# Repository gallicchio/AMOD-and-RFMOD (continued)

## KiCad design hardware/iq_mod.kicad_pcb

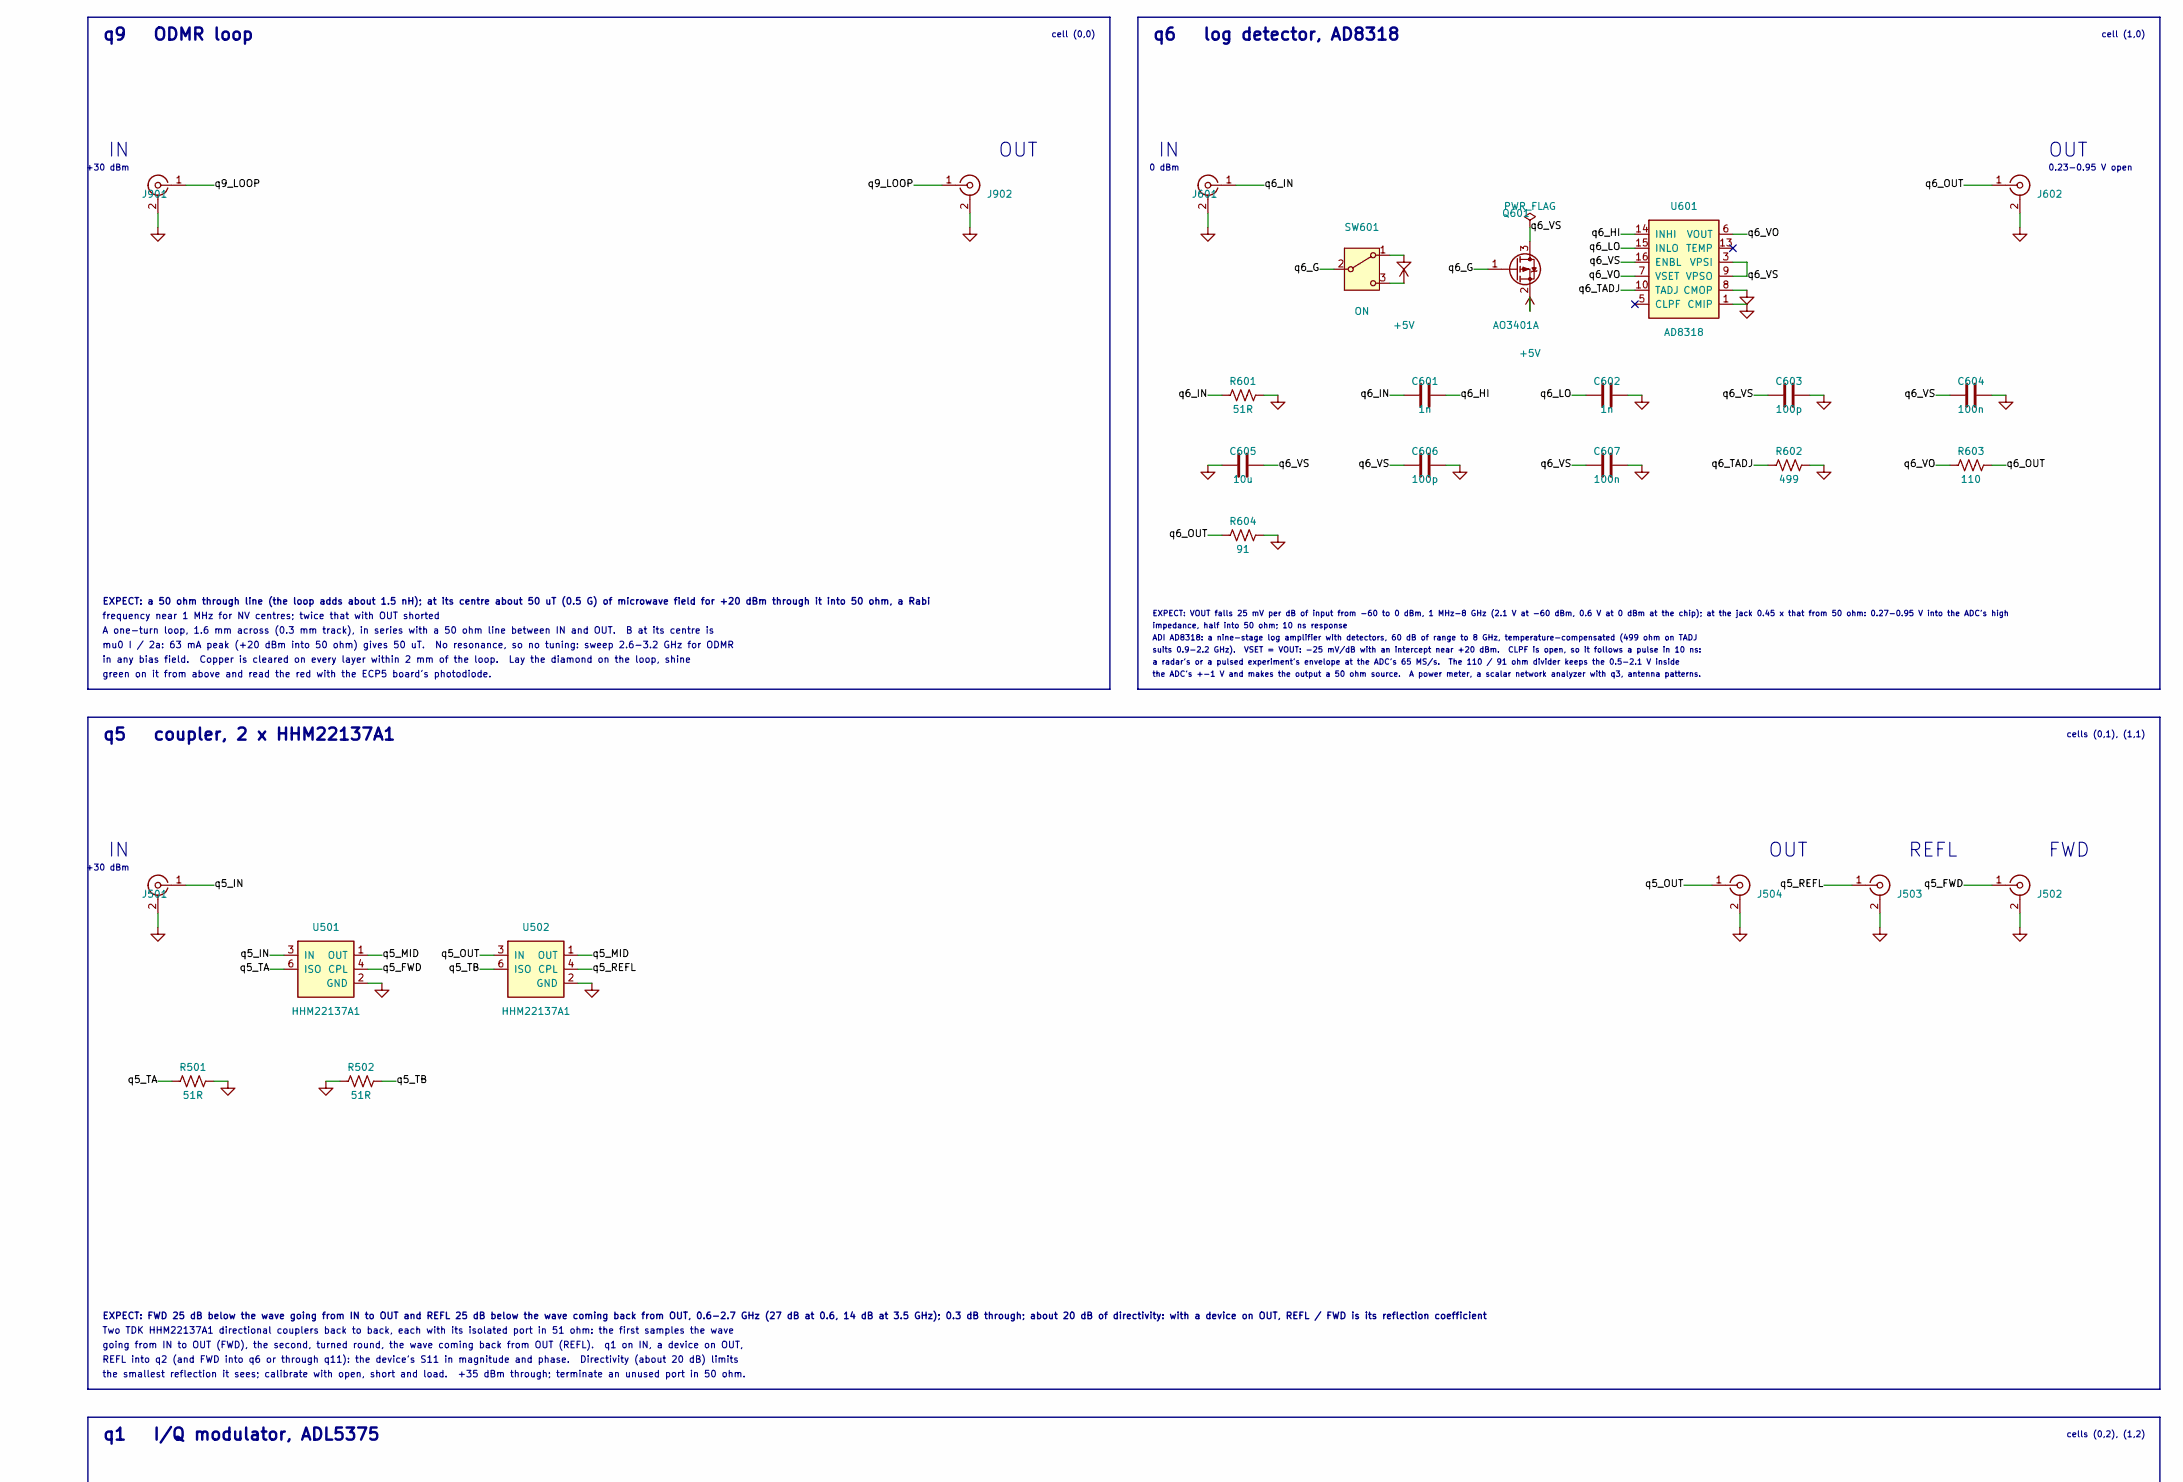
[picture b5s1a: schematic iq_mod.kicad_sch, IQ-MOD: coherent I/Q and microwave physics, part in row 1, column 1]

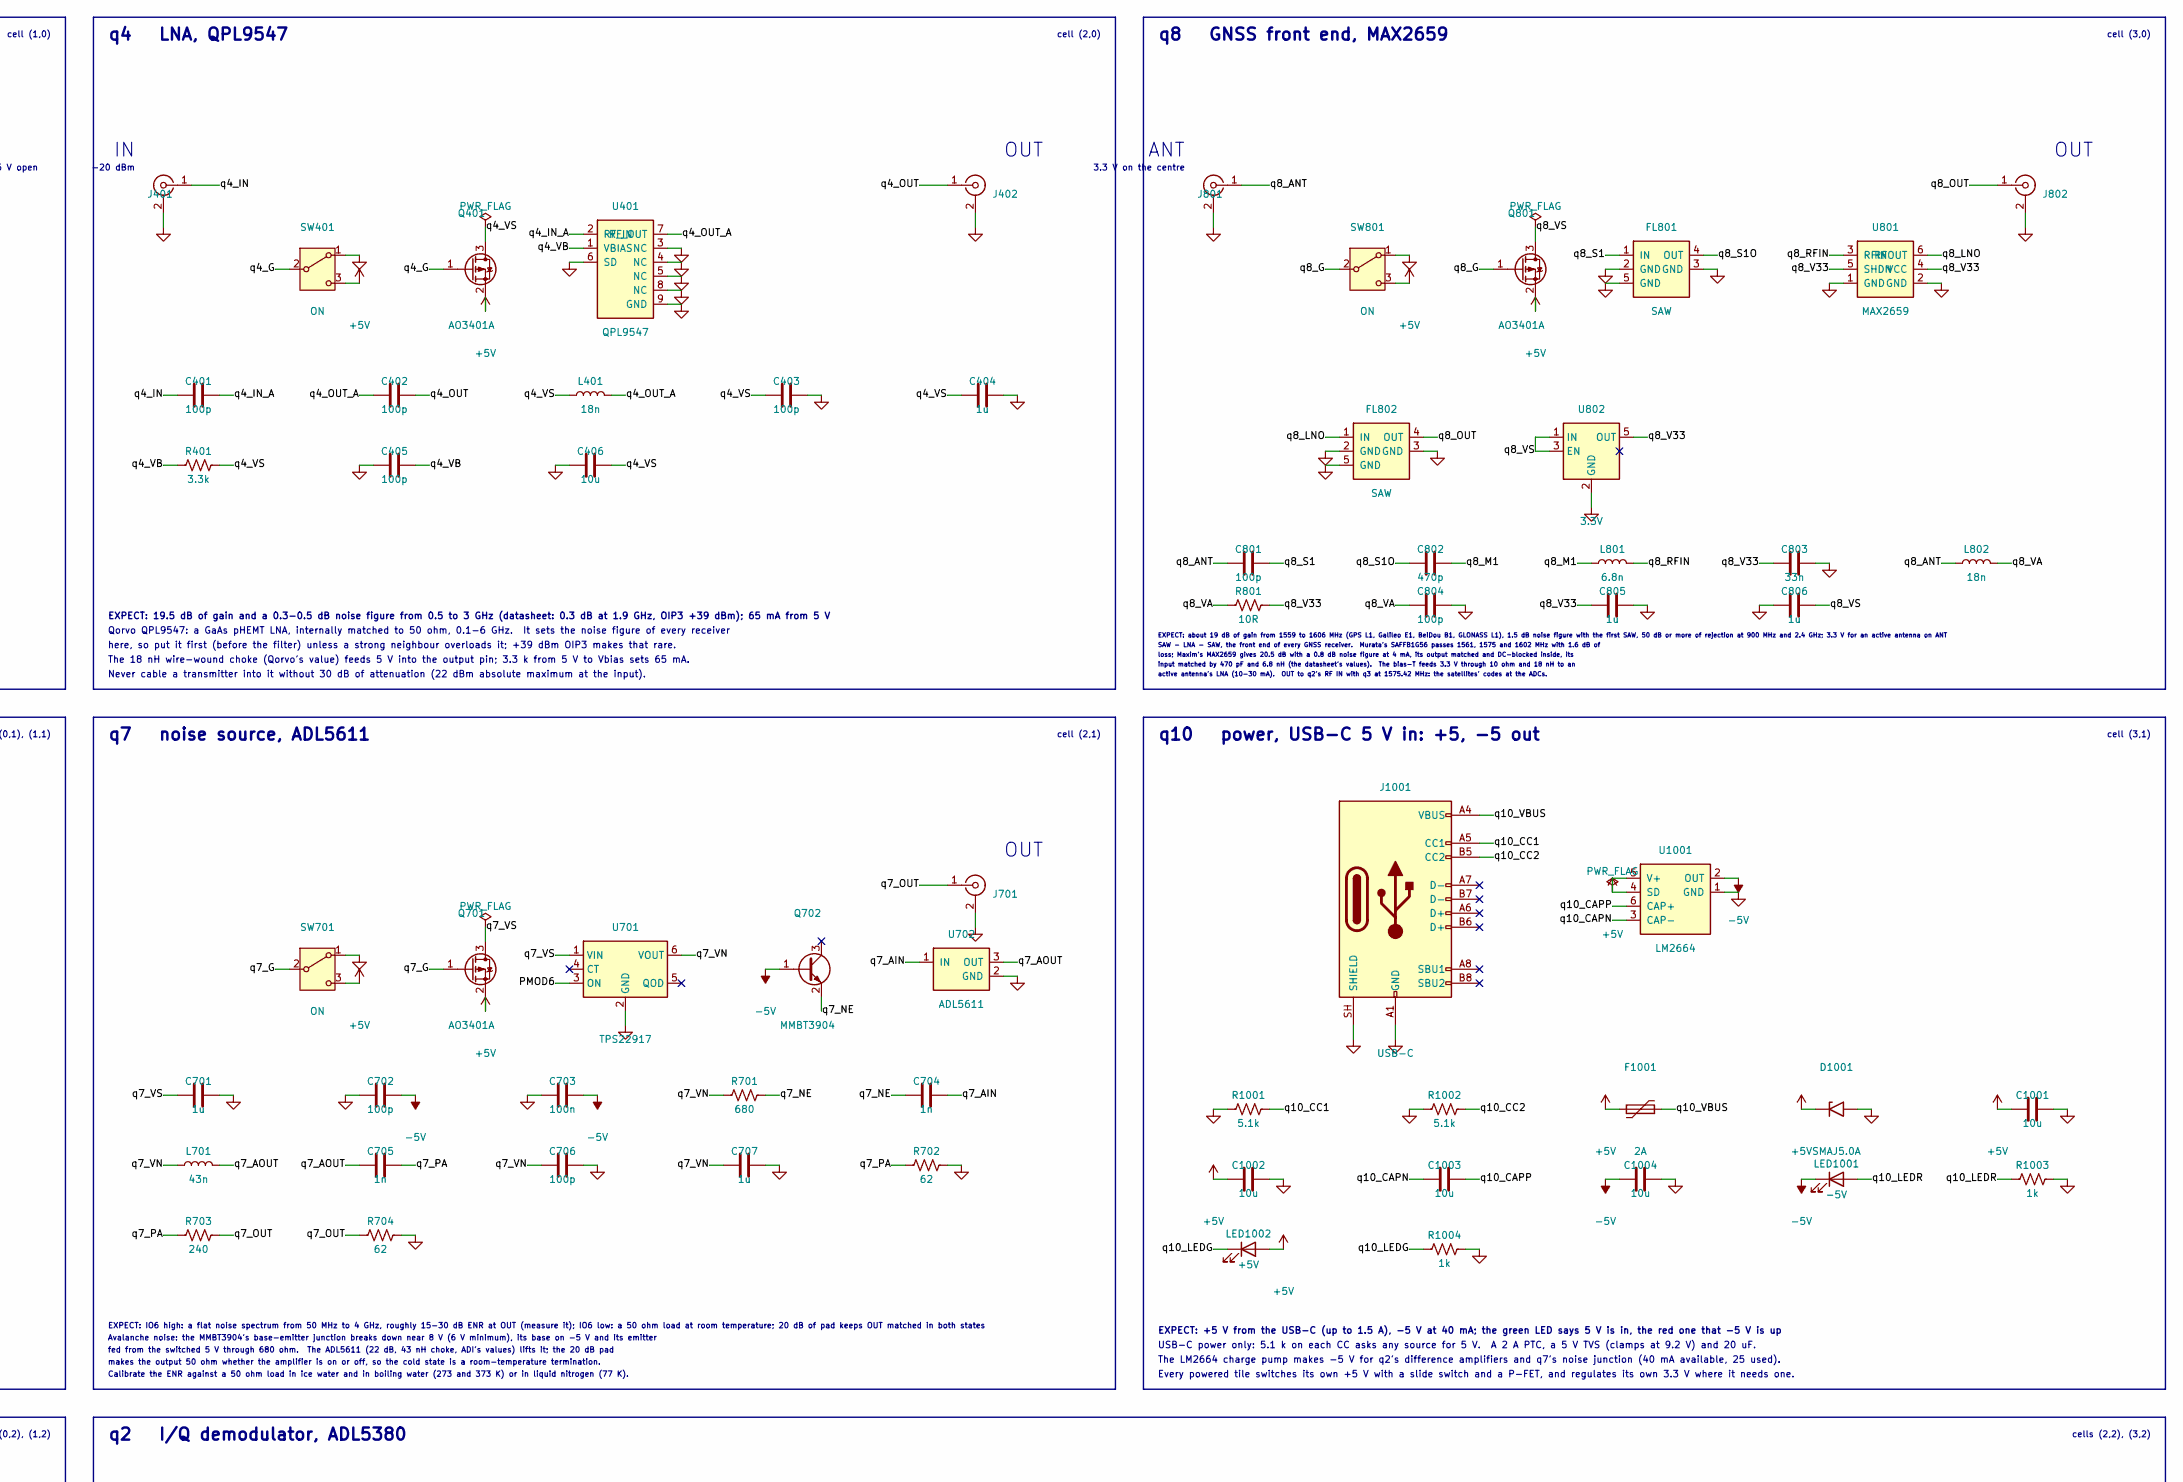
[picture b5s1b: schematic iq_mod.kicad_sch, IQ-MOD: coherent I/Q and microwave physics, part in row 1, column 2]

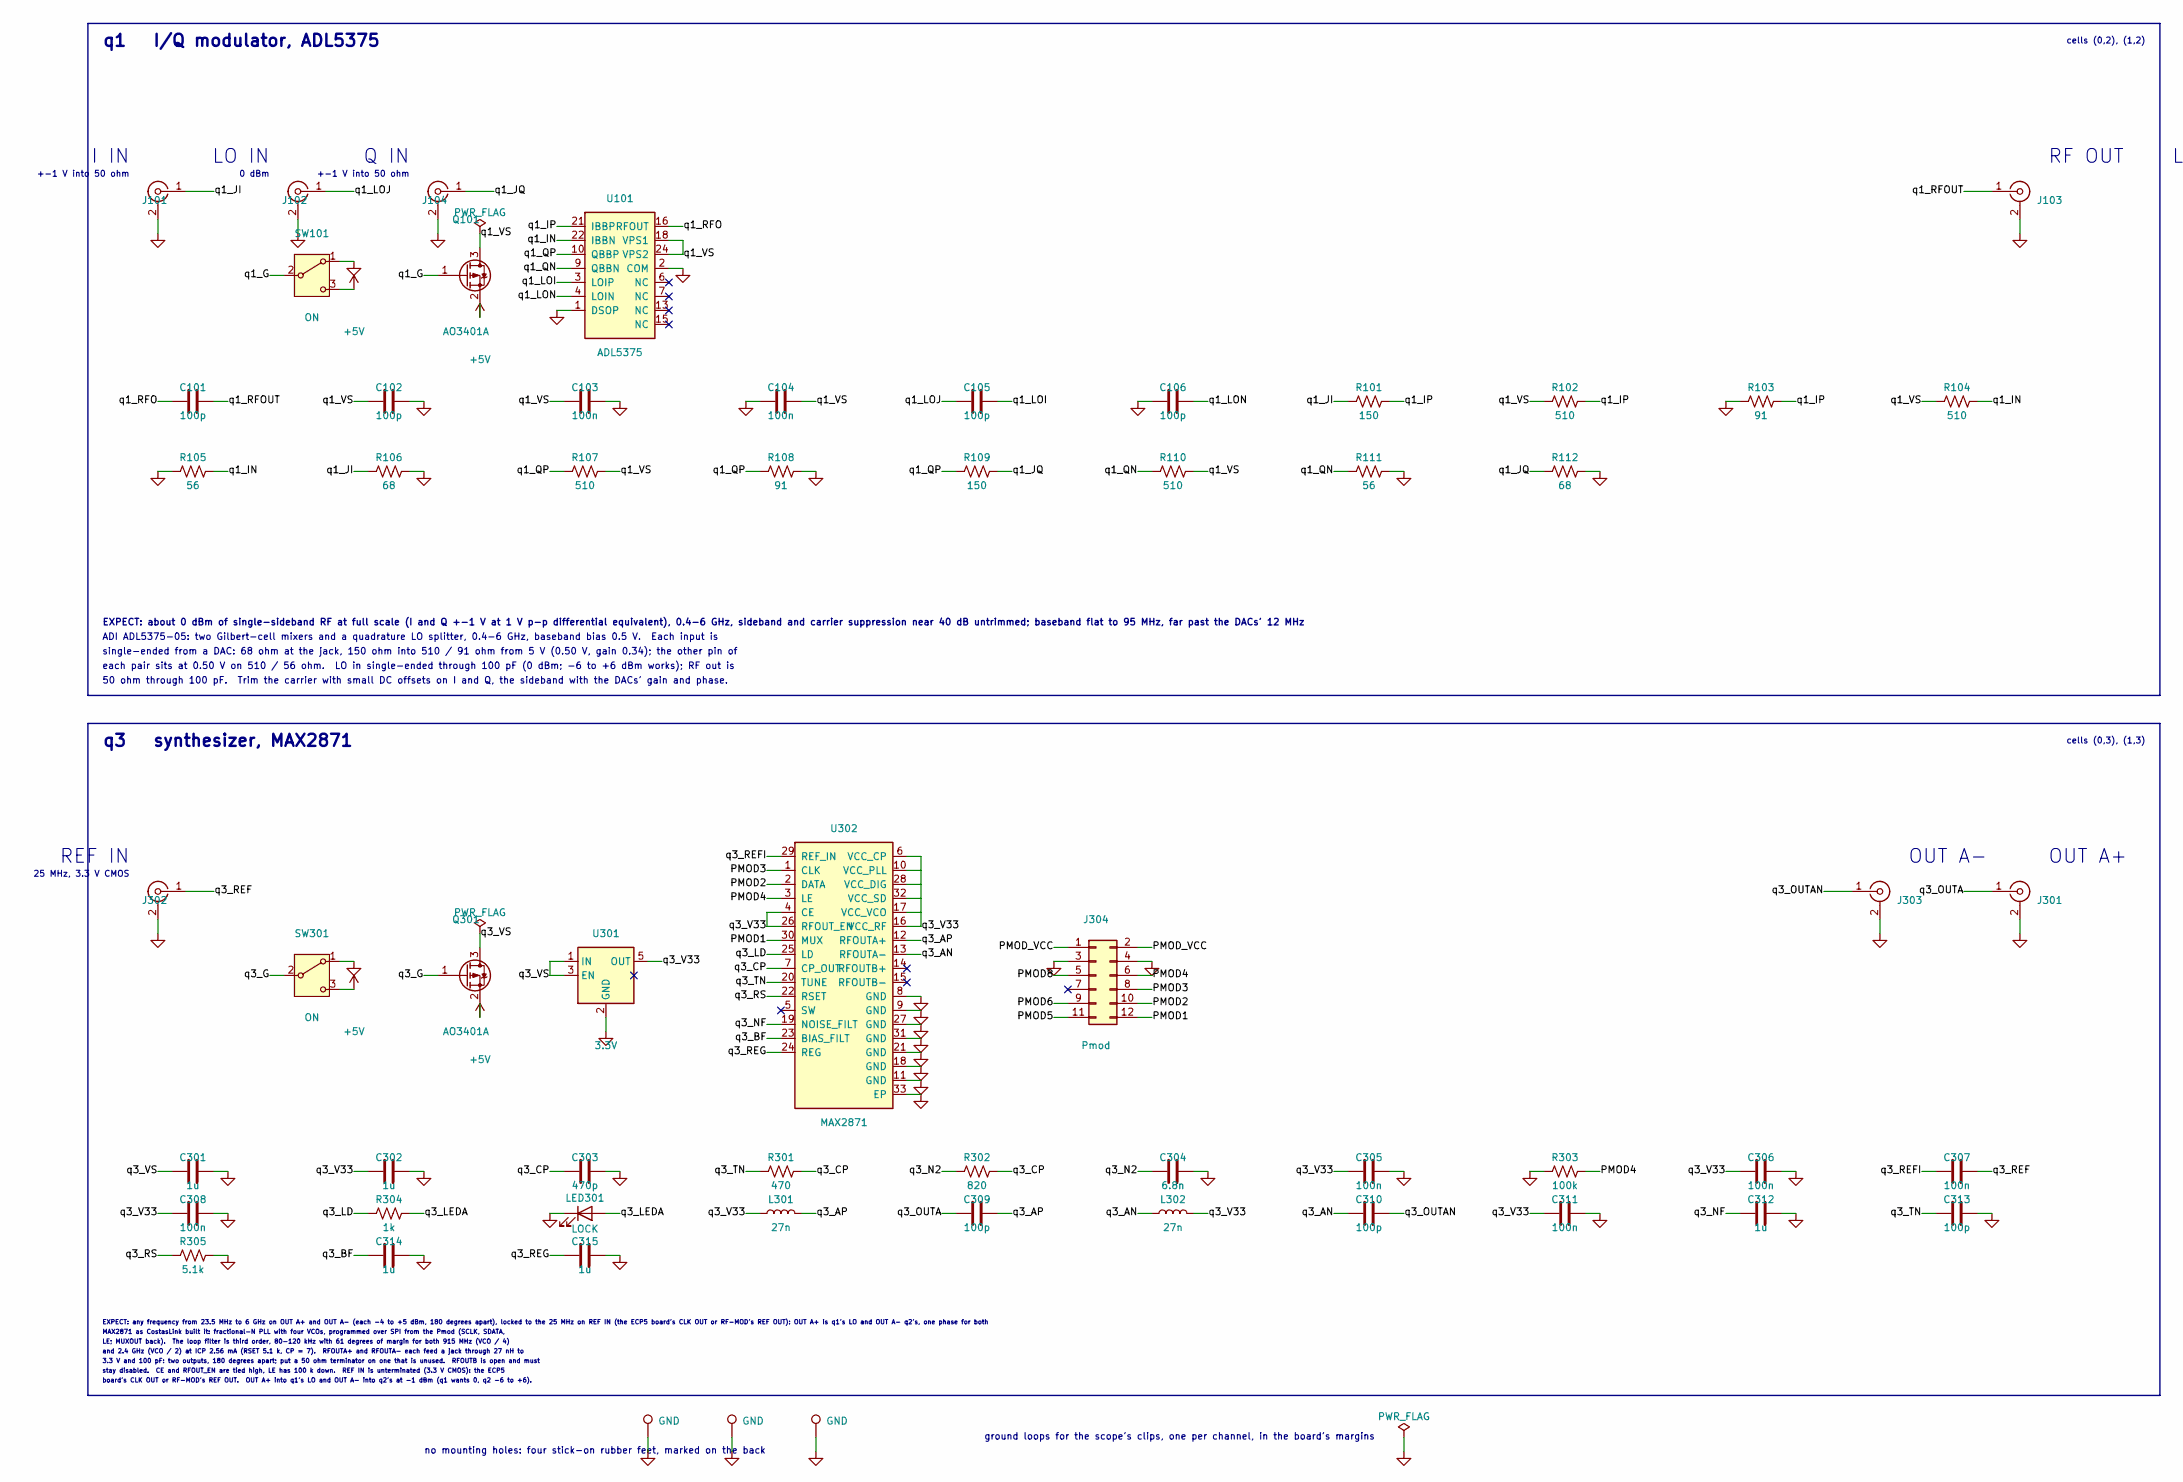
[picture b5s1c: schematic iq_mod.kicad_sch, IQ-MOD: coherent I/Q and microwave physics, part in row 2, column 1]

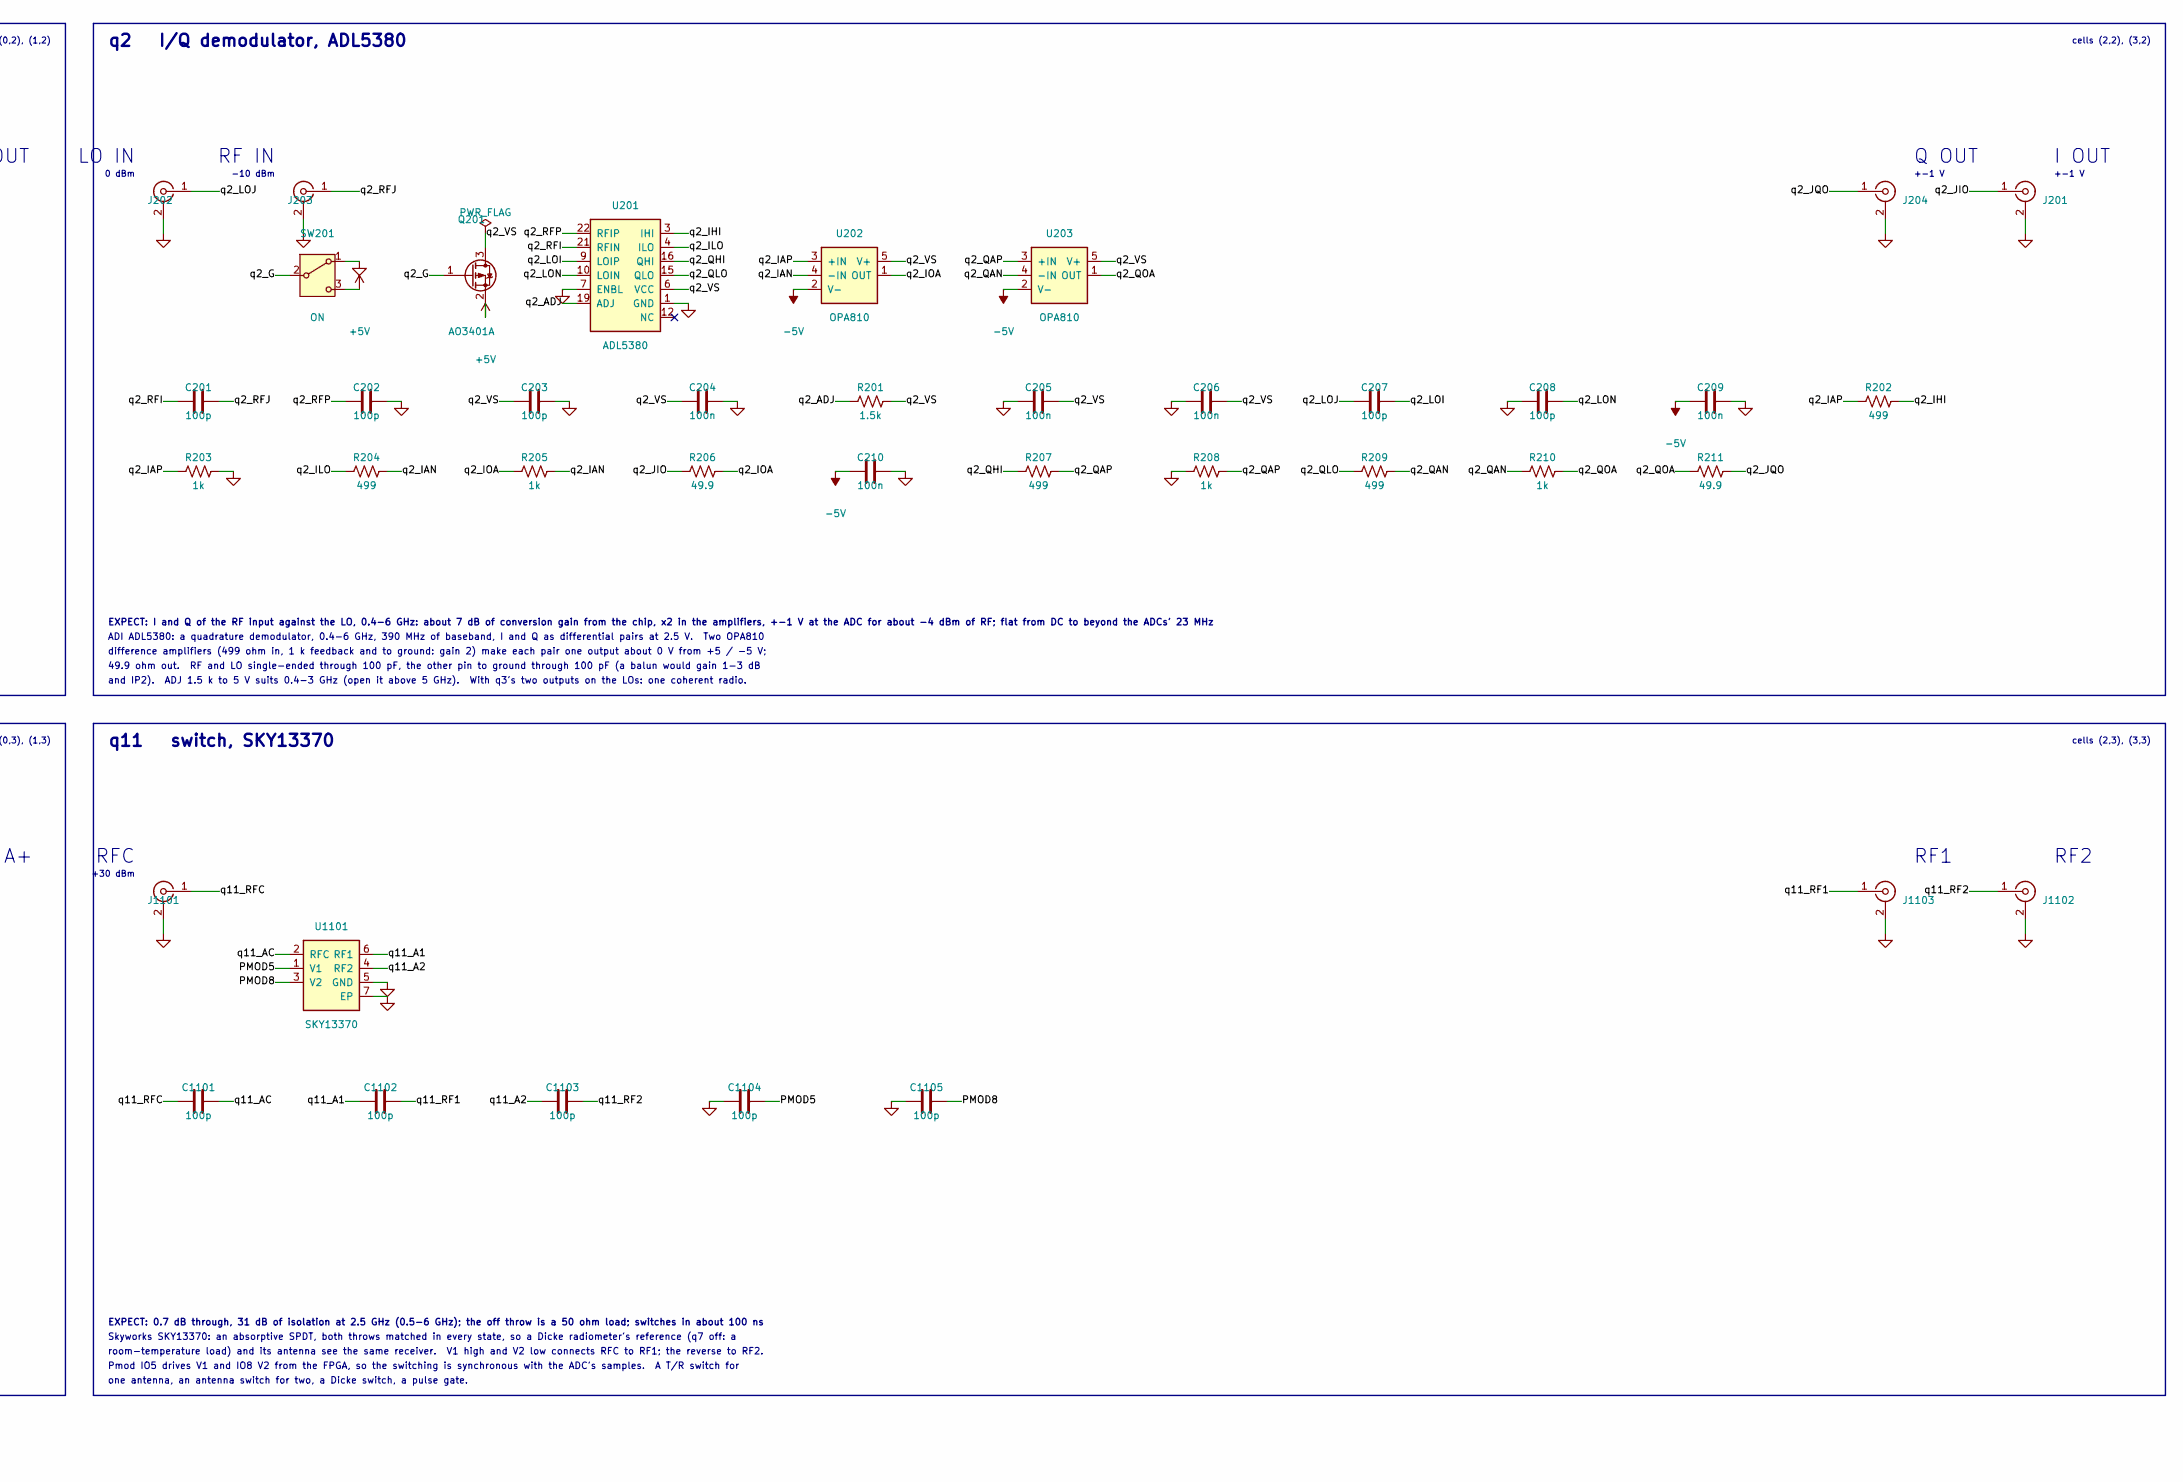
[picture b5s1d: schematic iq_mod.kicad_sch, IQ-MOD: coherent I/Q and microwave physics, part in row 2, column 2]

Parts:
C101, C102, C105, C106, C201, C202, C203, C207, C208, C309, C310, C401, C402, C403, C405, C603, C606, C702, C706, C801, C804, C1101, C1102, C1103, C1104, C1105: 100p; C_0402_1005Metric; MPN 0402CG101J500NT; LCSC C1546
C103, C104, C204, C205, C206, C209, C210, C305, C306, C307, C308, C311, C604, C607, C703: 100n; C_0402_1005Metric; MPN CL05B104KO5NNNC; LCSC C1525
C301, C302: 1u; C_0805_2012Metric; MPN CL21B105KBFNNNE; LCSC C28323
C303: 470p; C_0603_1608Metric; MPN 0603CG471J500NT; LCSC C36252
C304: 6.8n; C_0603_1608Metric; MPN GRM1885C1H682JA01D; LCSC C162241
C312, C314, C315, C404, C701, C707, C805, C806: 1u; C_0402_1005Metric; MPN CL05A105KP5NNNC; LCSC C14445
C313: 100p; C_0603_1608Metric; MPN CL10C101JB8NNNC; LCSC C14858
C406, C605, C1001, C1002, C1003, C1004: 10u; C_0805_2012Metric; MPN CL21A106KAYNNNE; LCSC C15850
C601, C602, C704, C705: 1n; C_0402_1005Metric; MPN 0402B102K500NT; LCSC C1523
C802: 470p; C_0402_1005Metric; MPN 0402CG471J500NT; LCSC C75274
C803: 33n; C_0402_1005Metric; MPN FCC0402B333K500AT; LCSC C7419416
D1001: SMAJ5.0A; D_SMA; MPN SMAJ5.0A; LCSC C78401
F1001: 2A; Fuse_1812_4532Metric; MPN MF-MSMF200-2; LCSC C210837
FL801, FL802: SAW; Filter_SAW_1109-5P_SAFFB1G56; MPN SAFFB1G56KB0F0AR1X; LCSC C91647
J101, J102, J103, J104, J201, J202, J203, J204, J301, J302, J303, J401, J402, J501, J502, J503, J504, J601, J602, J701, J801, J802, J901, J902, J1101, J1102, J1103: SMA; SMA_BWSMA-KE-Z001_Vertical; MPN BWSMA-KE-Z001; LCSC C496549
J304: Pmod; PinHeader_2x06_P2.54mm_Horizontal_PZ254R-12-12P; MPN PZ254R-12-12P; LCSC C492434
J1001: USB-C; USB_C_Receptacle_HRO_TYPE-C-31-M-12; MPN TYPE-C-31-M-12; LCSC C165948
L301, L302: 27n; L_0402_1005Metric; MPN LQW15AN27NG80D; LCSC C882469
L401, L802: 18n; L_0402_1005Metric; MPN LQW15AN18NG00D; LCSC C91622
L701: 43n; L_0603_1608Metric; MPN LQW18AN43NG00D; LCSC C113126
L801: 6.8n; L_0402_1005Metric; MPN LQW15AN6N8G00D; LCSC C82919
LED301: LOCK; LED_0805_2012Metric_Kbar; MPN NCD0805R1; LCSC C84256
LED1001: -5V; LED_0805_2012Metric_Kbar; MPN NCD0805R1; LCSC C84256
LED1002: +5V; LED_0805_2012Metric_Kbar; MPN KT-0805G; LCSC C2297
Q101, Q201, Q301, Q401, Q601, Q701, Q801: AO3401A; SOT-23; MPN AO3401A; LCSC C15127
Q702: MMBT3904; SOT-23; MPN MMBT3904(RANGE:100-300); LCSC C20526
R101, R109: 150; R_0402_1005Metric; MPN 0402WGF1500TCE; LCSC C25082
R102, R104, R107, R110: 510; R_0402_1005Metric; MPN 0402WGF5100TCE; LCSC C25123
R103, R108, R604: 91; R_0402_1005Metric; MPN 0402WGF910JTCE; LCSC C270574
R105, R111: 56; R_0402_1005Metric; MPN 0402WGF560JTCE; LCSC C25127
R106, R112: 68; R_0402_1005Metric; MPN 0402WGF680JTCE; LCSC C25131
R201: 1.5k; R_0402_1005Metric; MPN 0402WGF1501TCE; LCSC C25867
R202, R204, R207, R209, R602: 499; R_0402_1005Metric; MPN 0402WGF4990TCE; LCSC C4125
R203, R205, R208, R210, R304: 1k; R_0402_1005Metric; MPN 0402WGF1001TCE; LCSC C11702
R206, R211: 49.9; R_0402_1005Metric; MPN CRCW040249R9FKEDHP; LCSC C844112
R301: 470; R_0402_1005Metric; MPN 0402WGF4700TCE; LCSC C25117
R302: 820; R_0402_1005Metric; MPN 0402WGF8200TCE; LCSC C25135
R303: 100k; R_0402_1005Metric; MPN 0402WGF1003TCE; LCSC C25741
R305: 5.1k; R_0402_1005Metric; MPN 0402WGF5101TCE; LCSC C25905
R401: 3.3k; R_0402_1005Metric; MPN 0402WGF3301TCE; LCSC C25890
R501, R502, R601: 51R; R_0402_1005Metric; MPN 0402WGF510JTCE; LCSC C25125
R603: 110; R_0402_1005Metric; MPN 0402WGF1100TCE; LCSC C25078
R701: 680; R_0402_1005Metric; MPN 0402WGF6800TCE; LCSC C25130
R702, R704: 62; R_0402_1005Metric; MPN 0402WGF620JTCE; LCSC C4962
R703: 240; R_0402_1005Metric; MPN 0402WGF2400TCE; LCSC C25094
R801: 10R; R_0402_1005Metric; MPN 0402WGF100JTCE; LCSC C25077
R1001, R1002: 5.1k; R_0805_2012Metric; MPN 0805W8F5101T5E; LCSC C27834
R1003, R1004: 1k; R_0805_2012Metric; MPN 0805W8F1001T5E; LCSC C17513
SW101, SW201, SW301, SW401, SW601, SW701, SW801: ON; SW_SPDT_Shouhan_MSK12C02; MPN MSK12C02; LCSC C431540
TP9901, TP9902, TP9903: GND; TestPoint_Loop_RH-5019; MPN RH-5019; LCSC C5199800
U101: ADL5375; QFN-24-1EP_4x4mm_P0.5mm_EP2.5x2.5mm; MPN ADL5375-05ACPZ-R7; LCSC C579150
U201: ADL5380; QFN-24-1EP_4x4mm_P0.5mm_EP2.5x2.5mm; MPN ADL5380ACPZ-R7; LCSC C579152
U202, U203: OPA810; SOT-23-5; MPN OPA810IDBVR; LCSC C2833513
U301, U802: 3.3V; SOT-23-5; MPN TPS7A2033PDBVR; LCSC C2862740
U302: MAX2871; QFN-32-1EP_5x5mm_P0.5mm_EP3.1x3.1mm; MPN MAX2871ETJ+T; LCSC C7458627
U401: QPL9547; DFN-8-1EP_2x2mm_P0.5mm_EP0.9x1.6mm; MPN QPL9547TR7; LCSC C5367093
U501, U502: HHM22137A1; Coupler_1608-6P_HHM22137A1; MPN HHM22137A1; LCSC C415328
U601: AD8318; QFN-16-1EP_4x4mm_P0.65mm_EP2.1x2.1mm; MPN AD8318ACPZ-REEL7; LCSC C578694
U701: TPS22917; SOT-23-6; MPN TPS22917DBVR; LCSC C2681320
U702: ADL5611; SOT-89-3; MPN ADL5611ARKZ-R7; LCSC C208262
U801: MAX2659; UDFN-6_1.5x1.0mm_P0.5mm_MAX2659; MPN MAX2659ELT+T; LCSC C28043
U1001: LM2664; SOT-23-6; MPN LM2664M6X/NOPB; LCSC C108573
U1101: SKY13370; DFN-6-1EP_1.5x1.5mm_P0.5mm_SKY13370; MPN SKY13370-374LF; LCSC C105628

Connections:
+5V: C1001.1, C1002.1, D1001.1 (A1), F1001.1, LED1002.2 (A), Q101.2 (S), Q201.2 (S), Q301.2 (S), Q401.2 (S), Q601.2 (S), Q701.2 (S), Q801.2 (S), SW101.3 (C), SW201.3 (C), SW301.3 (C), SW401.3 (C), SW601.3 (C), SW701.3 (C), SW801.3 (C), U1001.4 (SD), U1001.5 (V+)
-5V: C209.1, C210.1, C702.2, C703.2, C1004.1, LED1001.1 (K), Q702.1 (B), U202.2 (V-), U203.2 (V-), U1001.2 (OUT)
/PMOD1: J304.12, U302.30 (MUX)
/PMOD2: J304.10, U302.2 (DATA)
/PMOD3: J304.8, U302.1 (CLK)
/PMOD4: J304.6, R303.2, U302.3 (LE)
/PMOD5: C1104.2, J304.11, U1101.1 (V1)
/PMOD6: J304.9, U701.3 (ON)
/PMOD8: C1105.2, J304.5, U1101.3 (V2)
/PMOD_VCC: J304.1, J304.2
/q1_G: Q101.1 (G), SW101.2 (B)
/q1_IN: R104.2, R105.2, U101.22 (IBBN)
/q1_IP: R101.2, R102.2, R103.2, U101.21 (IBBP)
/q1_JI: J101.1 (In), R101.1, R106.1
/q1_JQ: J104.1 (In), R109.2, R112.1
/q1_LOI: C105.2, U101.3 (LOIP)
/q1_LOJ: C105.1, J102.1 (In)
/q1_LON: C106.2, U101.4 (LOIN)
/q1_QN: R110.1, R111.1, U101.9 (QBBN)
/q1_QP: R107.1, R108.1, R109.1, U101.10 (QBBP)
/q1_RFO: C101.1, U101.16 (RFOUT)
/q1_RFOUT: C101.2, J103.1 (In)
/q1_VS: C102.1, C103.1, C104.2, Q101.3 (D), R102.1, R104.1, R107.2, R110.2, U101.18 (VPS1), U101.24 (VPS2)
/q2_ADJ: R201.1, U201.19 (ADJ)
/q2_G: Q201.1 (G), SW201.2 (B)
/q2_IAN: R204.2, R205.2, U202.4 (-IN)
/q2_IAP: R202.1, R203.1, U202.3 (+IN)
/q2_IHI: R202.2, U201.3 (IHI)
/q2_ILO: R204.1, U201.4 (ILO)
/q2_IOA: R205.1, R206.2, U202.1 (OUT)
/q2_JIO: J201.1 (In), R206.1
/q2_JQO: J204.1 (In), R211.2
/q2_LOI: C207.2, U201.9 (LOIP)
/q2_LOJ: C207.1, J202.1 (In)
/q2_LON: C208.2, U201.10 (LOIN)
/q2_QAN: R209.2, R210.1, U203.4 (-IN)
/q2_QAP: R207.2, R208.2, U203.3 (+IN)
/q2_QHI: R207.1, U201.16 (QHI)
/q2_QLO: R209.1, U201.15 (QLO)
/q2_QOA: R210.2, R211.1, U203.1 (OUT)
/q2_RFI: C201.1, U201.21 (RFIN)
/q2_RFJ: C201.2, J203.1 (In)
/q2_RFP: C202.1, U201.22 (RFIP)
/q2_VS: C203.1, C204.1, C205.2, C206.2, Q201.3 (D), R201.2, U201.6 (VCC), U201.13 (VCC), U201.24 (VCC), U202.5 (V+), U203.5 (V+)
/q3_AN: C310.1, L302.1, U302.13 (RFOUTA-)
/q3_AP: C309.2, L301.2, U302.12 (RFOUTA+)
/q3_BF: C314.1, U302.23 (BIAS_FILT)
/q3_CP: C303.1, R301.2, R302.2, U302.7 (CP_OUT)
/q3_G: Q301.1 (G), SW301.2 (B)
/q3_LD: R304.1, U302.25 (LD)
/q3_LEDA: LED301.2 (A), R304.2
/q3_N2: C304.1, R302.1
/q3_NF: C312.1, U302.19 (NOISE_FILT)
/q3_OUTA: C309.1, J301.1 (In)
/q3_OUTAN: C310.2, J303.1 (In)
/q3_REF: C307.2, J302.1 (In)
/q3_REFI: C307.1, U302.29 (REF_IN)
/q3_REG: C315.1, U302.24 (REG)
/q3_RS: R305.1, U302.22 (RSET)
/q3_TN: C313.1, R301.1, U302.20 (TUNE)
/q3_V33: C302.1, C305.1, C306.1, C308.1, C311.1, L301.1, L302.2, U301.5 (OUT), U302.4 (CE), U302.6 (VCC_CP), U302.10 (VCC_PLL), U302.16 (VCC_RF), U302.17 (VCC_VCO), U302.26 (RFOUT_EN), U302.28 (VCC_DIG), U302.32 (VCC_SD)
/q3_VS: C301.1, Q301.3 (D), U301.1 (IN), U301.3 (EN)
/q4_G: Q401.1 (G), SW401.2 (B)
/q4_IN: C401.1, J401.1 (In)
/q4_IN_A: C401.2, U401.2 (RF_IN)
/q4_OUT: C402.2, J402.1 (In)
/q4_OUT_A: C402.1, L401.2, U401.7 (RF_OUT)
/q4_VB: C405.2, R401.1, U401.1 (VBIAS)
/q4_VS: C403.1, C404.1, C406.2, L401.1, Q401.3 (D), R401.2
/q5_FWD: J502.1 (In), U501.4 (CPL)
/q5_IN: J501.1 (In), U501.3 (IN)
/q5_MID: U501.1 (OUT), U502.1 (OUT)
/q5_OUT: J504.1 (In), U502.3 (IN)
/q5_REFL: J503.1 (In), U502.4 (CPL)
/q5_TA: R501.1, U501.6 (ISO)
/q5_TB: R502.2, U502.6 (ISO)
/q6_G: Q601.1 (G), SW601.2 (B)
/q6_HI: C601.2, U601.14 (INHI)
/q6_IN: C601.1, J601.1 (In), R601.1
/q6_LO: C602.1, U601.15 (INLO)
/q6_OUT: J602.1 (In), R603.2, R604.1
/q6_TADJ: R602.1, U601.10 (TADJ)
/q6_VO: R603.1, U601.6 (VOUT), U601.7 (VSET)
/q6_VS: C603.1, C604.1, C605.2, C606.1, C607.1, Q601.3 (D), U601.3 (VPSI), U601.4 (VPSI), U601.9 (VPSO), U601.16 (ENBL)
/q7_AIN: C704.2, U702.1 (IN)
/q7_AOUT: C705.1, L701.2, U702.3 (OUT)
/q7_G: Q701.1 (G), SW701.2 (B)
/q7_NE: C704.1, Q702.2 (E), R701.2
/q7_OUT: J701.1 (In), R703.2, R704.1
/q7_PA: C705.2, R702.1, R703.1
/q7_VN: C706.1, C707.1, L701.1, R701.1, U701.6 (VOUT)
/q7_VS: C701.1, Q701.3 (D), U701.1 (VIN)
/q8_ANT: C801.1, J801.1 (In), L802.1
/q8_G: Q801.1 (G), SW801.2 (B)
/q8_LNO: FL802.1 (IN), U801.6 (RFOUT)
/q8_M1: C802.2, L801.1
/q8_OUT: FL802.4 (OUT), J802.1 (In)
/q8_RFIN: L801.2, U801.3 (RFIN)
/q8_S1: C801.2, FL801.1 (IN)
/q8_S1O: C802.1, FL801.4 (OUT)
/q8_V33: C803.1, C805.1, R801.2, U801.4 (VCC), U801.5 (SHDN), U802.5 (OUT)
/q8_VA: C804.1, L802.2, R801.1
/q8_VS: C806.2, Q801.3 (D), U802.1 (IN), U802.3 (EN)
/q9_LOOP: J901.1 (In), J902.1 (In)
/q10_CAPN: C1003.1, U1001.3 (CAP-)
/q10_CAPP: C1003.2, U1001.6 (CAP+)
/q10_CC1: J1001.A5 (CC1), R1001.2
/q10_CC2: J1001.B5 (CC2), R1002.2
/q10_LEDG: LED1002.1 (K), R1004.1
/q10_LEDR: LED1001.2 (A), R1003.1
/q10_VBUS: F1001.2, J1001.A4 (VBUS), J1001.A9 (VBUS), J1001.B4 (VBUS), J1001.B9 (VBUS)
/q11_A1: C1102.1, U1101.6 (RF1)
/q11_A2: C1103.1, U1101.4 (RF2)
/q11_AC: C1101.2, U1101.2 (RFC)
/q11_RF1: C1102.2, J1103.1 (In)
/q11_RF2: C1103.2, J1102.1 (In)
/q11_RFC: C1101.1, J1101.1 (In)
GND: C102.2, C103.2, C104.1, C106.1, C202.2, C203.2, C204.2, C205.1, C206.1, C208.1, C209.2, C210.2, C301.2, C302.2, C303.2, C304.2, C305.2, C306.2, C308.2, C311.2, C312.2, C313.2, C314.2, C315.2, C403.2, C404.2, C405.1, C406.1, C602.2, C603.2, C604.2, C605.1, C606.2, C607.2, C701.2, C702.1, C703.1, C706.2, C707.2, C803.2, C804.2, C805.2, C806.1, C1001.2, C1002.2, C1004.2, C1104.1, C1105.1, D1001.2 (A2), FL801.2 (GND), FL801.3 (GND), FL801.5 (GND), FL802.2 (GND), FL802.3 (GND), FL802.5 (GND), J101.2 (Ext), J102.2 (Ext), J103.2 (Ext), J104.2 (Ext), J201.2 (Ext), J202.2 (Ext), J203.2 (Ext), J204.2 (Ext), J301.2 (Ext), J302.2 (Ext), J303.2 (Ext), J304.3, J304.4, J401.2 (Ext), J402.2 (Ext), J501.2 (Ext), J502.2 (Ext), J503.2 (Ext), J504.2 (Ext), J601.2 (Ext), J602.2 (Ext), J701.2 (Ext), J801.2 (Ext), J802.2 (Ext), J901.2 (Ext), J902.2 (Ext), J1001.A1 (GND), J1001.A12 (GND), J1001.B1 (GND), J1001.B12 (GND), J1001.SH (SHIELD), J1101.2 (Ext), J1102.2 (Ext), J1103.2 (Ext), LED301.1 (K), R103.1, R105.1, R106.2, R108.2, R111.2, R112.2, R203.2, R208.1, R303.1, R305.2, R501.2, R502.1, R601.2, R602.2, R604.2, R702.2, R704.2, R1001.1, R1002.1, R1003.2, R1004.2, SW101.1 (A), SW201.1 (A), SW301.1 (A), SW401.1 (A), SW601.1 (A), SW701.1 (A), SW801.1 (A), TP9901.1, TP9902.1, TP9903.1, U101.1 (DSOP), U101.2 (COM), U101.5 (COM), U101.8 (COM), U101.11 (COM), U101.12 (COM), U101.14 (COM), U101.17 (COM), U101.19 (COM), U101.20 (COM), U101.23 (COM), U101.25 (COM), U201.1 (GND), U201.2 (GND), U201.5 (GND), U201.7 (ENBL), U201.8 (GND), U201.11 (GND), U201.14 (GND), U201.17 (GND), U201.18 (GND), U201.20 (GND), U201.23 (GND), U201.25 (GND), U301.2 (GND), U302.8 (GND), U302.9 (GND), U302.11 (GND), U302.18 (GND), U302.21 (GND), U302.27 (GND), U302.31 (GND), U302.33 (EP), U401.3 (NC), U401.4 (NC), U401.5 (NC), U401.6 (SD), U401.8 (NC), U401.9 (GND), U501.2 (GND), U501.5 (GND), U502.2 (GND), U502.5 (GND), U601.1 (CMIP), U601.2 (CMIP), U601.8 (CMOP), U601.11 (CMIP), U601.12 (CMIP), U601.17 (CMIP), U701.2 (GND), U702.2 (GND), U801.1 (GND), U801.2 (GND), U802.2 (GND), U1001.1 (GND), U1101.5 (GND), U1101.7 (EP)

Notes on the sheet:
+30 dBm
OUT
SAW - LNA - SAW, the front end of every GNSS receiver. Murata's SAFFB1G56 passes 1561, 1575 and 1602 MHz with 1.6 dB of
Q IN
cells (2,2), (3,2)
active antenna's LNA (10-30 mA). OUT to q2's RF IN with q3 at 1575.42 MHz: the satellites' codes at the ADCs.
MAX2871 as CostasLink built it: fractional-N PLL with four VCOs, programmed over SPI from the Pmod (SCLK, SDATA,
one antenna, an antenna switch for two, a Dicke switch, a pulse gate.
cell (2,1)
the ADC's +-1 V and makes the output a 50 ohm source. A power meter, a scalar network analyzer with q3, antenna patterns.
0.23-0.95 V open
OUT A-
cell (2,0)
0 dBm
3.3 V and 100 pF: two outputs, 180 degrees apart; put a 50 ohm terminator on one that is unused. RFOUTB is open and must
LE; MUXOUT back). The loop filter is third order, 80-120 kHz with 61 degrees of margin for both 915 MHz (VCO / 4)
+-1 V into 50 ohm
EXPECT: a 50 ohm through line (the loop adds about 1.5 nH); at its centre about 50 uT (0.5 G) of microwave field for +20 dBm through it into 50 ohm, a Rabi
The 18 nH wire-wound choke (Qorvo's value) feeds 5 V into the output pin; 3.3 k from 5 V to Vbias sets 65 mA.
+-1 V
q11 switch, SKY13370
green on it from above and read the red with the ECP5 board's photodiode.
and IP2). ADJ 1.5 k to 5 V suits 0.4-3 GHz (open it above 5 GHz). With q3's two outputs on the LOs: one coherent radio.
difference amplifiers (499 ohm in, 1 k feedback and to ground: gain 2) make each pair one output about 0 V from +5 / -5 V;
I IN
board's CLK OUT or RF-MOD's REF OUT. OUT A+ into q1's LO and OUT A- into q2's at -1 dBm (q1 wants 0, q2 -6 to +6).
frequency near 1 MHz for NV centres; twice that with OUT shorted
RF OUT
RF IN
q2 I/Q demodulator, ADL5380
impedance, half into 50 ohm; 10 ns response
49.9 ohm out. RF and LO single-ended through 100 pF, the other pin to ground through 100 pF (a balun would gain 1-3 dB
25 MHz, 3.3 V CMOS
q9 ODMR loop
EXPECT: +5 V from the USB-C (up to 1.5 A), -5 V at 40 mA; the green LED says 5 V is in, the red one that -5 V is up
REF IN
cells (2,3), (3,3)
RF2
A one-turn loop, 1.6 mm across (0.3 mm track), in series with a 50 ohm line between IN and OUT. B at its centre is
Never cable a transmitter into it without 30 dB of attenuation (22 dBm absolute maximum at the input).

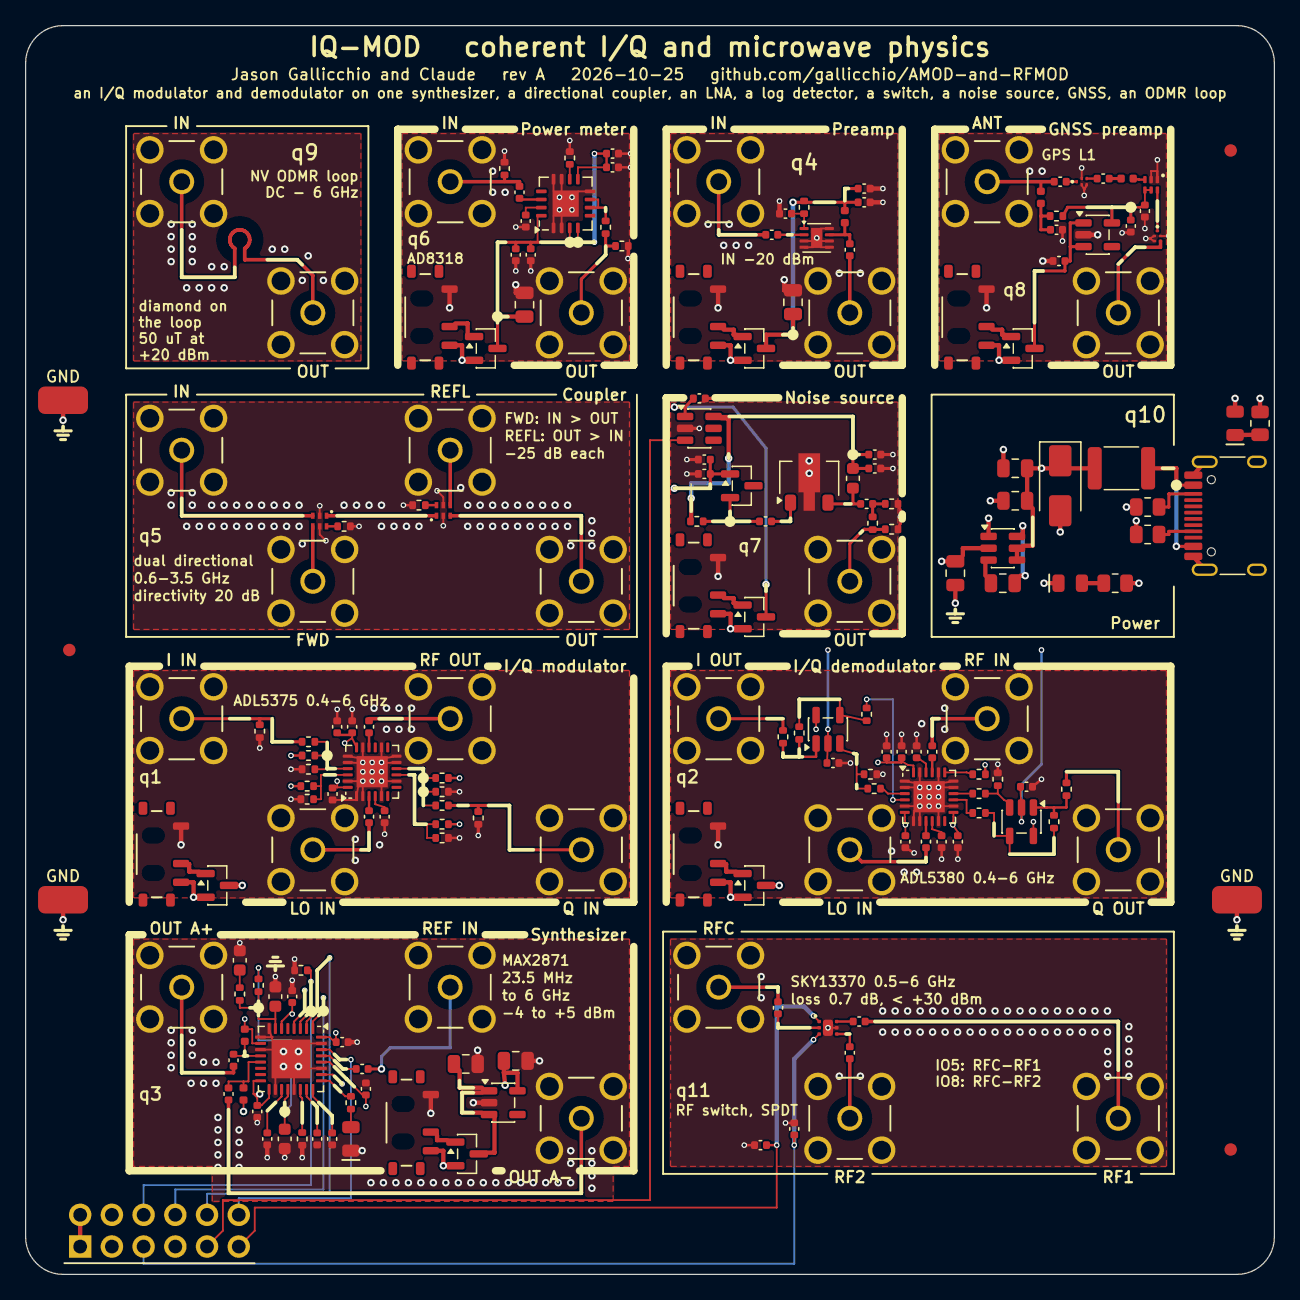
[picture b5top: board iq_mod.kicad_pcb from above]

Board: 4 copper layers, 100.0 x 100.0 mm, 186 parts (0 on the bottom side), 118 nets.
